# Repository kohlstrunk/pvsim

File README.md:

PVSIM

PV-Modul-Simulator
- getestet an Hoymiles HMS-800W-2T
- erlaubt DC-seitige Einstellung der Einspeiseleistung

Enthält:
- WinAVR-Projekt
- Eagle-Schaltplan und Layout
- Fertigungsdaten

Entwicklungsstand
- Erprobung 2-Kanalig an beiden separaten MPPT-Kanälen
- Erprobung 1-kanalig mit parallel geschalteten MPPT-Kanälen
- Erprobung mit Si-H-Brücke 50V 50A bei 62kHz Schaltfrequenz

Perspektive:
- Umstellung auf 250kHz GaN-Halbbrücke 20A mit parallel geschalteten MPPT-Kanälen

Links:
- https://www.mikrocontroller.net/topic/585740
- https://epc-co.com/epc/products/gan-fets-and-ics/epc23109

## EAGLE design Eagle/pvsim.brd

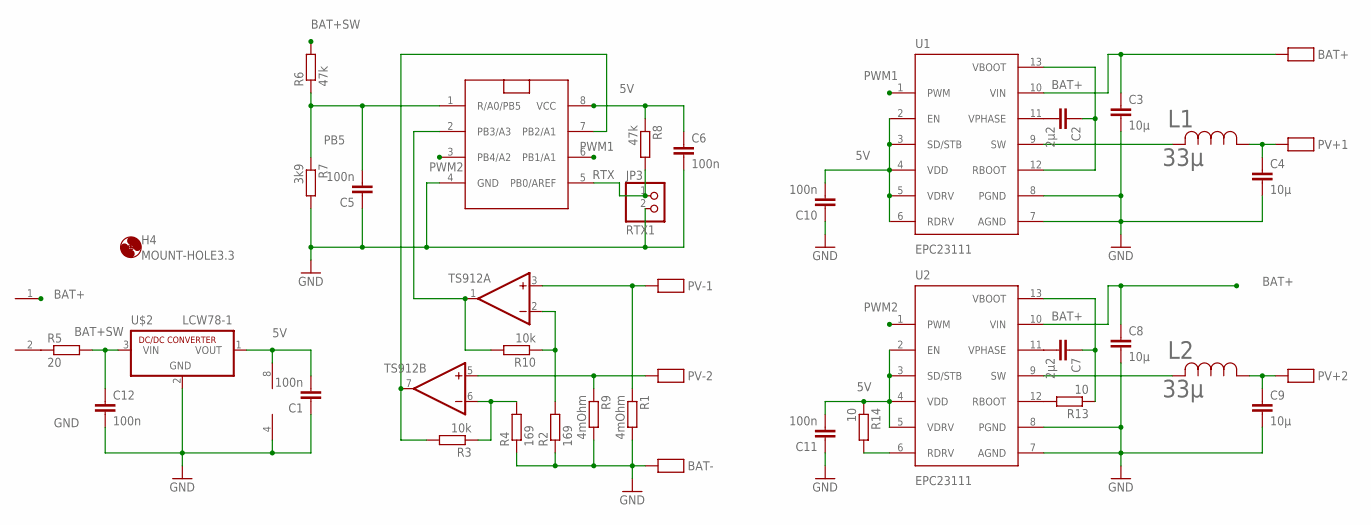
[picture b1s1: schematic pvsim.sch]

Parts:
BAT+: SMD_10X5
BAT-: SMD_10X5
C1, C5, C6, C10, C11, C12: 100n; C0805
C2: 2µ2; C0805K
C3, C4, C8, C9: 10µ; C1210K
C7: 2µ2; C1206K
FK1: Start; DG250-3.5-2
H4: MOUNT-HOLE3.3; 3,3
JP3: RTX1; 1X02
L1, L2: 33µ; IND_PA4349.333ANLT_PUL-M
PV+1, PV+2: SMD_10X5
PV-1, PV-2: SMD_10X5
R1, R9: 4mOhm; R2512
R2, R4: 169; R0805
R3, R10: 10k; R0805
R5: 20; 0207/10
R6, R8: 47k; R0805
R7: 3k9; R0805
R13, R14: 10; R0805
TS912: 2AMP_P8+4D; SO08
U1, U2: EPC23111; EPC23111_QFN13_EPC_LP
U$2: LCW78-1; SIP3
U$4: FUNKY; FUNKYTINY

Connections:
5V: C1.2, C6.1, C10.2, C11.2, R8.1, R14.1, TS912.8 (V+), U1.2 (EN), U1.3 (SD/STB), U1.4 (VDD), U1.5 (VDRV), U1.6 (RDRV), U2.2 (EN), U2.3 (SD/STB), U2.4 (VDD), U2.5 (VDRV), U$2.1 (VOUT), U$4.8 (VCC)
BAT+: BAT+.P$1, C3.1, C8.1, FK1.1, U1.10 (VIN), U2.10 (VIN)
BAT+SW: C12.1, R5.2, R6.2, U$2.3 (VIN)
BAT-: R9.2
GND: BAT-.P$1, C1.1, C3.2, C4.2, C5.1, C6.2, C8.2, C9.2, C10.1, C11.1, C12.2, JP3.2, R1.2, R2.1, R4.1, R7.2, TS912.4 (V-), U1.7 (AGND), U1.8 (PGND), U2.7 (AGND), U2.8 (PGND), U$2.2 (GND), U$4.4 (GND)
IPV1: PV-1.P$1, R1.1, TS912.3 (+IN)
IPV2: PV-2.P$1, R9.1, TS912.5 (+IN)
unnamed: R10.2, TS912.1 (OUT), U$4.2 (PB3/A3)
unnamed: R2.2, R10.1, TS912.2 (-IN)
unnamed: R3.2, TS912.7 (OUT), U$4.7 (PB2/A1)
unnamed: R3.1, R4.2, TS912.6 (-IN)
unnamed: FK1.2, R5.1
unnamed: C2.1, U1.12 (RBOOT), U1.13 (VBOOT)
unnamed: C2.2, U1.11 (VPHASE)
unnamed: C4.1, L1.1, PV+1.P$1
unnamed: L1.2, U1.9 (SW)
unnamed: C7.1, R13.1, U2.13 (VBOOT)
unnamed: C7.2, U2.11 (VPHASE)
unnamed: L2.2, U2.9 (SW)
unnamed: C9.1, L2.1, PV+2.P$1
unnamed: R13.2, U2.12 (RBOOT)
PB5: C5.2, R6.1, R7.1, U$4.1 (R/A0/PB5)
PWM1: U1.1 (PWM), U$4.6 (PB1/A1)
PWM2: U2.1 (PWM), U$4.3 (PB4/A2)
RTX: JP3.1, R8.2, U$4.5 (PB0/AREF)

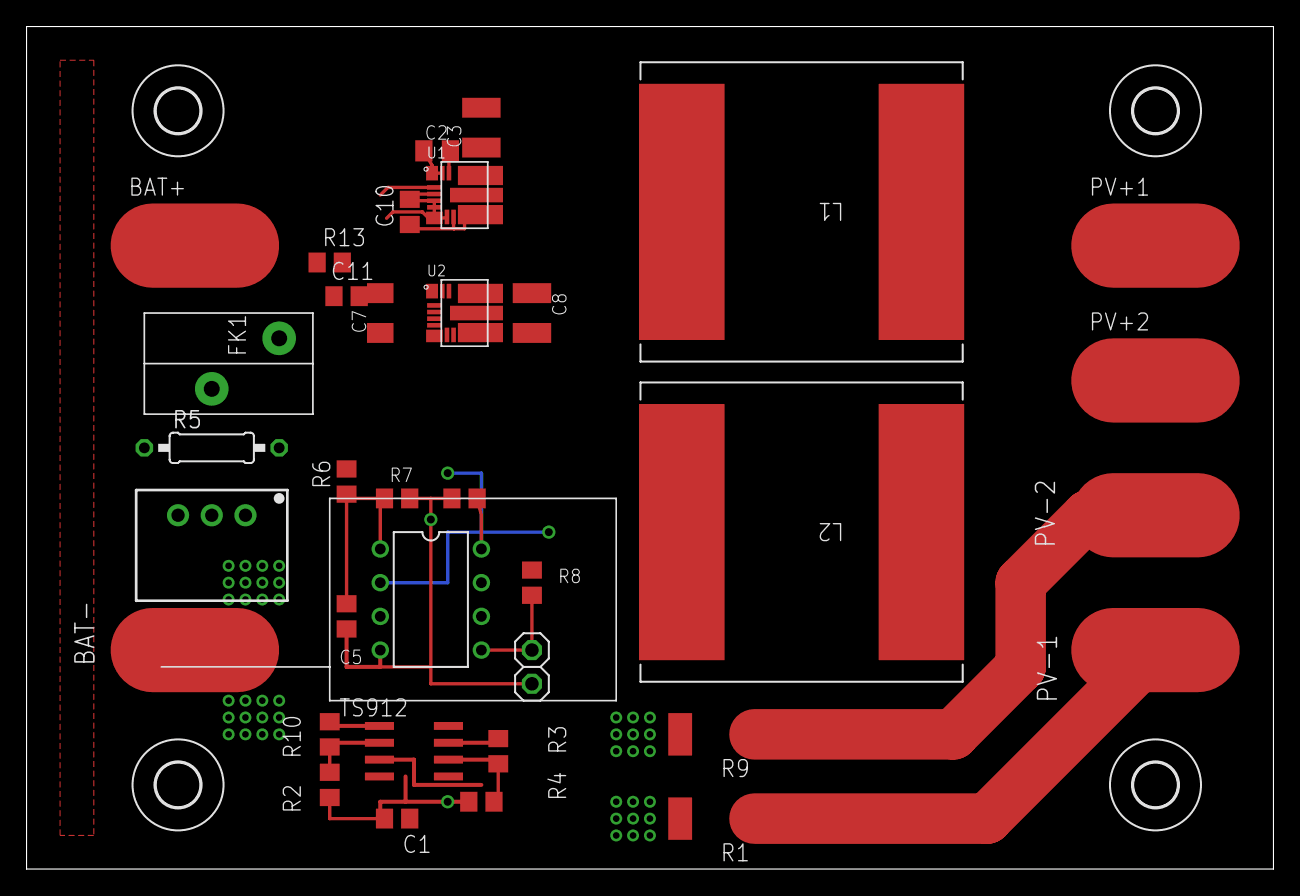
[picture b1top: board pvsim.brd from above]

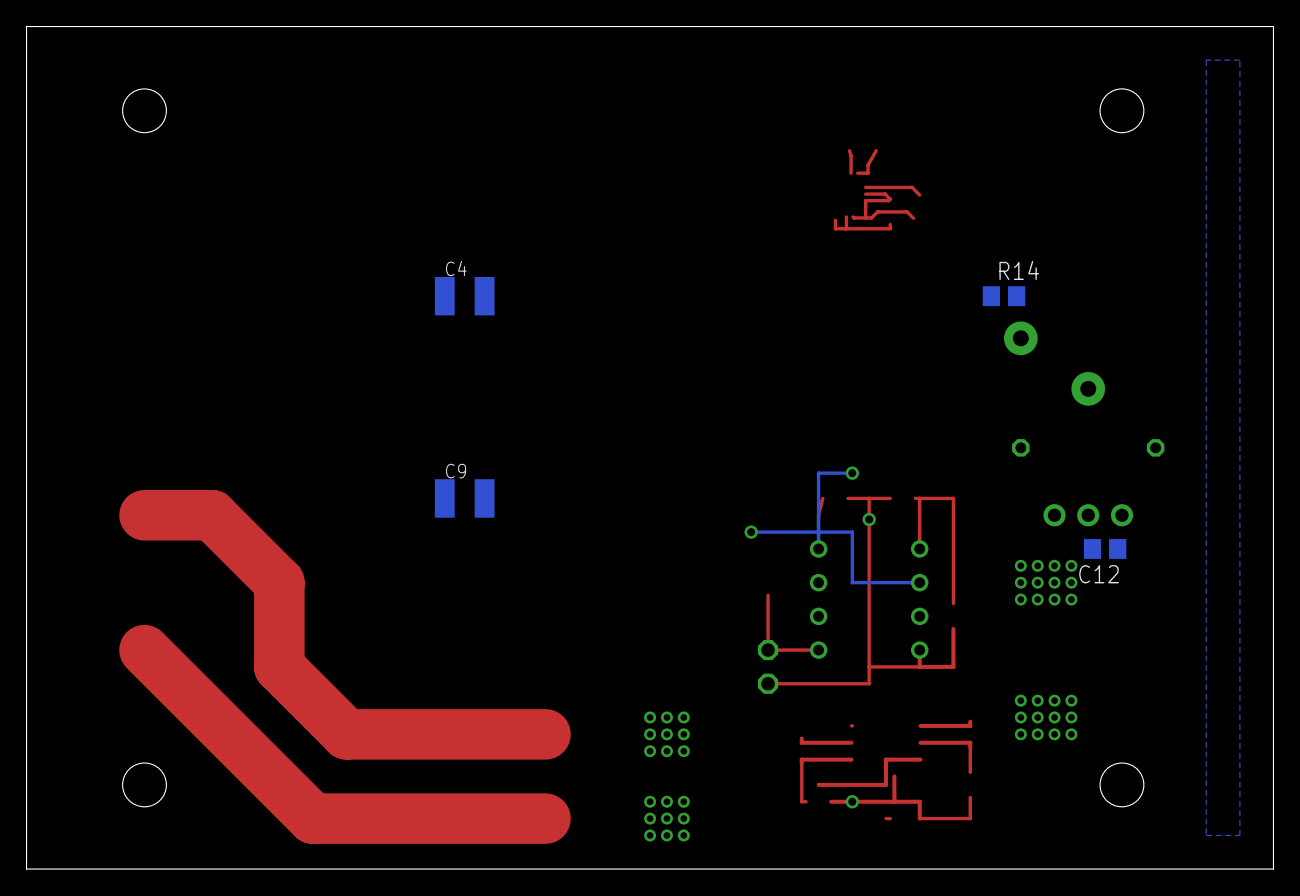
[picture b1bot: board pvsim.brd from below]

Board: 2 copper layers, 94.0 x 63.5 mm, 43 parts (4 on the bottom side), 24 nets.

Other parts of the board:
H1, H2, H3: MOUNT-HOLE3.3; 3,3

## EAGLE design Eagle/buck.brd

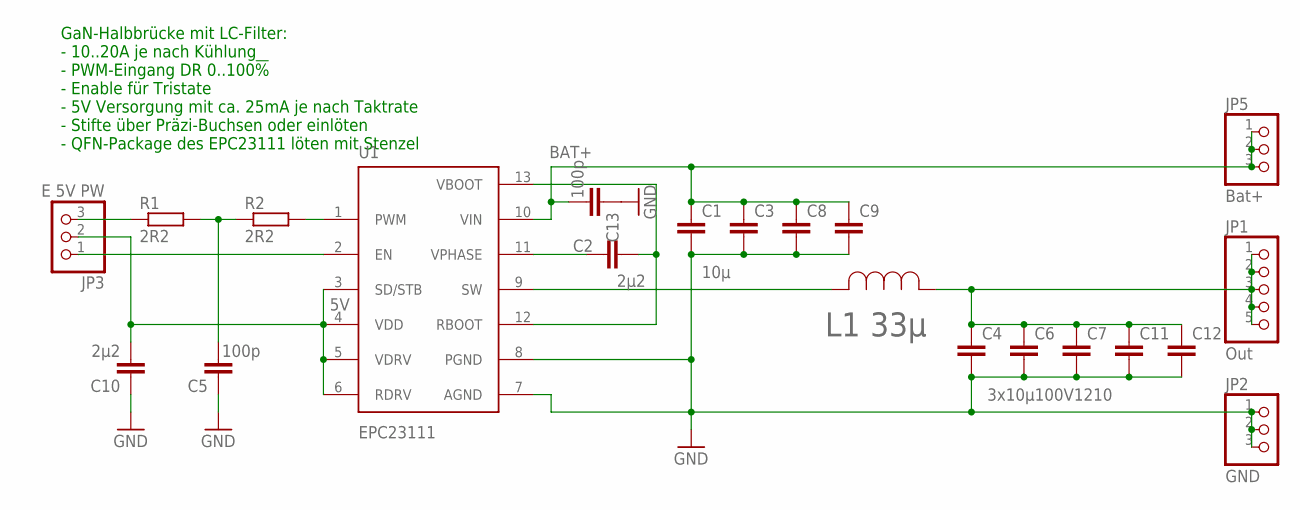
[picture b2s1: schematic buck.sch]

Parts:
C1, C4: 10µ; C1210K
C2, C10: 2µ2; C0603K
C3, C7, C8, C9, C11, C12: 10µ100V1210; C1210K
C5: 100p; C0603K
C6: 3x10µ100V1210; C1210K
C13: 100p; C1206K
JP1: Out; 1X05
JP2: GND; 1X03
JP3: E 5V PW; 1X03
JP5: Bat+; 1X03
L1: 33µ; IND_PA4349.333ANLT_PUL-M
R1, R2: 2R2; R0603
U1: EPC23111; EPC23111_QFN13_EPC_LP

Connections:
5V: C10.2, JP3.2, U1.3 (SD/STB), U1.4 (VDD), U1.5 (VDRV), U1.6 (RDRV)
BAT+: C1.1, C3.1, C8.1, C9.1, C13.2, JP5.1, JP5.2, JP5.3, U1.10 (VIN)
GND: C1.2, C3.2, C4.2, C5.1, C6.2, C7.2, C8.2, C9.2, C10.1, C11.2, C12.2, C13.1, JP2.1, JP2.2, JP2.3, U1.7 (AGND), U1.8 (PGND)
unnamed: C5.2, R1.2, R2.1
unnamed: R2.2, U1.1 (PWM)
unnamed: JP3.1, U1.2 (EN)
unnamed: JP3.3, R1.1
unnamed: C2.1, U1.12 (RBOOT), U1.13 (VBOOT)
unnamed: C2.2, U1.11 (VPHASE)
SW: L1.2, U1.9 (SW)
UOUT: C4.1, C6.1, C7.1, C11.1, C12.1, JP1.1, JP1.2, JP1.3, JP1.4, JP1.5, L1.1

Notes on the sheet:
GaN-Halbbrücke mit LC-Filter: - 10..20A je nach Kühlung - PWM-Eingang DR 0..100!% - Enable für Tristate - 5V Versorgung mit ca. 25mA je nach Taktrate - Stifte über Präzi-Buchsen oder einlöten - QFN-Package des EPC23111 löten mit Stenzel

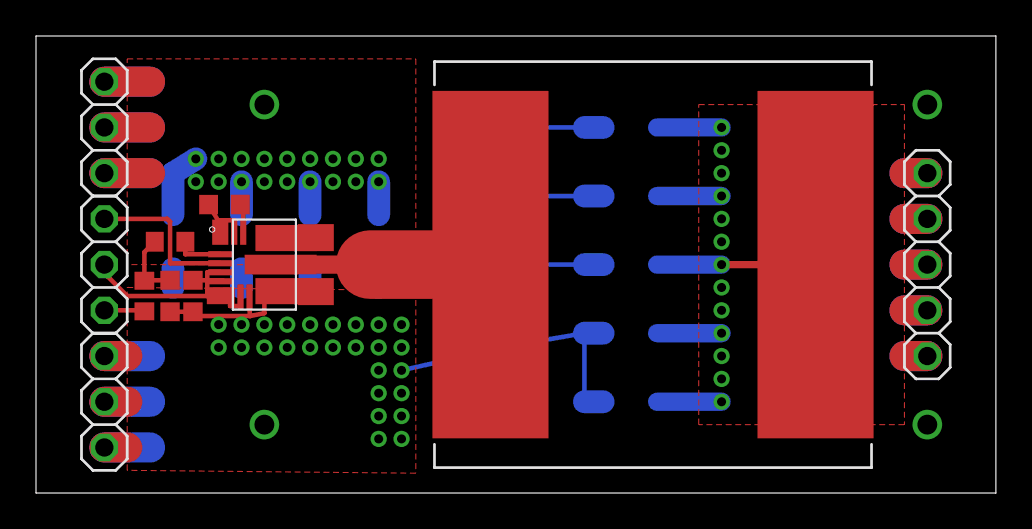
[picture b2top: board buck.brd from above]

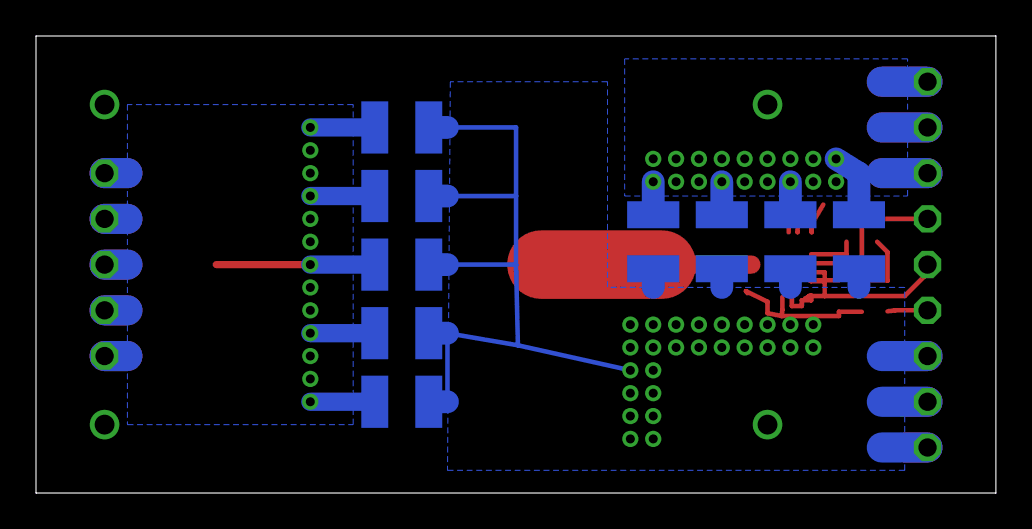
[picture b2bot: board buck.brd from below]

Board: 2 copper layers, 53.3 x 25.4 mm, 21 parts (9 on the bottom side), 11 nets.

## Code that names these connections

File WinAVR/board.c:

/* 
Hardwareschicht: ISR, Portzugriffe,  

Hardware: Attiny85 mit Fuse: SELFPRGEN, SPIEN, DIS BODLEVEL, 8MHz 64ms


PB0 - RTX/Bootloader
PB1 - PWM
PB2 - LED 
PB3 - Iout-
PB4 - Iout+ 
PB5 - Ubat, Reset

Funktionen: 
- Soft-UART in ISR
- App-Timing
*/

#include <avr/interrupt.h>
#include "board.h"
#include "daten.h"

void rx(void);
void tx(void);
void tim(void);

ISR (PCINT0_vect){								// lauscht auf PinChange Ereignis 
uint8_t b;										// differenz
	b=TCNT0;									// Timerwert speichern für RX 			
	if (!RTX_S){ 								// HL-Flanke
		if((outran==TNO)&(rxi==RDY)){			// Leitung frei? -> RX	
			if (intran==TNO) intran=TYES;		// Leitung ist für Lesen blockiert
			if (b>=(TBIT-TABT)) OCR0B=b-(TBIT-TABT);else OCR0B=b+TABT;// TimerB vorbereiten Achtung Wertebereich
			if(TBIF_S) TBIF_D;rxi=STA;			// ggf. auch Flag löschen - wirklich wichtig
			}// endif 
		}// Ende RX
}												// Ende PC-IRQ

ISR (TIM0_COMPB_vect){							// TBIT/2
//	tx();rx();									// Soft-UART
	rx();tx();									// kritisch ist RX +-30µs
	tim();										// Timing Zeug
}   

void tim(void){
//uint8_t t0=TCNT0;dt_us=TCNT0-t0;
//uint8_t t0=rtt; dtt=rtt-t0;
//long t0=get_ms();tms=get_ms()-t0;	

	if ((rtusec+=TBIT)>999999L) {rtusec-=1000000L;rtsec++; tick ^= 0x01;} 	// µs-Überlauf -> sec++
//	rtt++;
}

void tx(void){
static uint8_t c=0; uint8_t b=0;
	if (outran!=TNO){										// Senden
		switch(txi){
			case STA: b=0;c=uc;					txi++;	break;	// Startbit
			default:if (c&1)b=1;else b=0;c>>=1;	txi++;	break;	// Datenbits
			case STP: b=1;						txi++;	break;	// Stopbit 
			case RDY: b=1;								break;
			}
		if(b==0){RTX_PD;}if(b==1){RTX_PU;}				// physische Ausgabe
		}// end if
}

void rx(void){
static uint8_t cmdi=0,cmdti,c=0;							// Takt,cmdtimeindex,bits,bitnr
uint8_t b=0;												// byte,
	if (intran!=TNO){//49µs									// Empfangen zuerst 
	  	b=RTX_S;
	  	switch (rxi){
			case STA:cmdti=0;	  c=0;		rxi++;	break;	// Startbit
			default: c>>=1;if(b) c|=0x80;	rxi++;	break;	// Datenbits lesen
			case STP:
				if (c=='\n') c='\0';						// nur NL beendet schnell
				cmd[cmdi++]=c;cmd[cmdi]='\0';rxi++;			// Schreiben samt '\0'
				if (c=='\0') 		  {cmdf=JA;	 cmdi=0;intran=TNO;}		// Abschluss sofort
				if ((cmdi+1)>CMDMAXI) {cmdf=NEIN;cmdi=0;intran=TNO;}break;	// Abbruch 												
			case RDY:if (++cmdti>TOUT){cmdf=JA;	 cmdi=0;intran=TNO;}break;	// Abschluss nach 25ms
			}	
	  	}
}

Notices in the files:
parts and their libraries:
COPYRIGHT: Copyright (C) 2021 Ultra Librarian. All rights reserved.
